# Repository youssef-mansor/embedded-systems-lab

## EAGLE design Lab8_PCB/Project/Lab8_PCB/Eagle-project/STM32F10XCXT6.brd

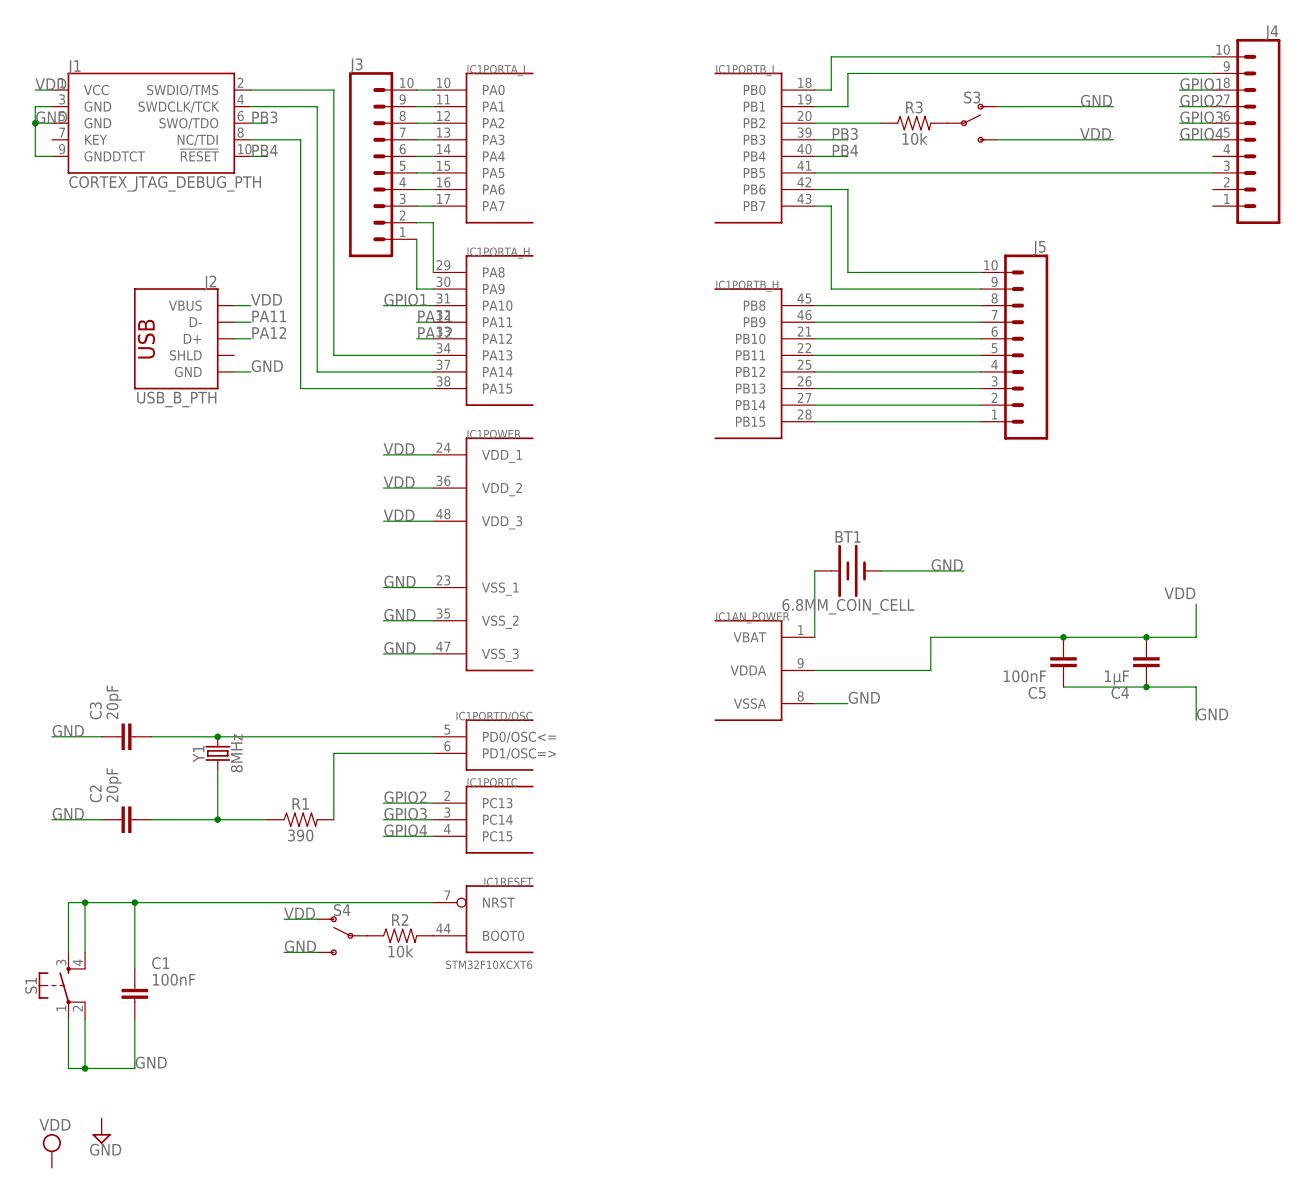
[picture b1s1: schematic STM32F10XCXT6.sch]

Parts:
BT1: 6.8MM_COIN_CELL; BATTCON-6.8MM
IC1: STM32F10XCXT6; TQFP48
J1: CORTEX_JTAG_DEBUG_PTH; 2X5-PTH-1.27MM
J2: USB_B_PTH; USB-B-PTH
J3, J4, J5: CONN_10"; 1X10
R1: 390; 0603
R2, R3: 10k; 0402
S1: MOMENTARY-SWITCH-SPST-2-SMD-4.6X2.8MM; TACTILE_SWITCH_SMD_4.6X2.8MM
S3, S4: SWITCH-SPDT-PTH-8.6X4.3MM; SWITCH_SPDT_8.6X4.3MM
Y1: 8MHz; CRYSTAL-PTH-2X6-CYL

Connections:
GND: BT1.-, IC1.8 (VSSA), IC1.23 (VSS_1), IC1.35 (VSS_2), IC1.47 (VSS_3), J1.3 (GND), J1.5 (GND), J1.9 (GNDDTCT), J2.GND, S1.1, S1.2, S3.1 (O), S4.3 (S)
GPIO1: IC1.31 (PA10), J4.8
GPIO2: IC1.2 (PC13), J4.7
GPIO3: IC1.3 (PC14), J4.6
GPIO4: IC1.4 (PC15), J4.5
unnamed: IC1.10 (PA0), J3.10
unnamed: IC1.7 (NRST), S1.3, S1.4
unnamed: IC1.5 (PD0/OSC<=), Y1.2
unnamed: IC1.6 (PD1/OSC=>), R1.2
unnamed: R1.1, Y1.1
unnamed: IC1.44 (BOOT0), R2.2
unnamed: R2.1, S4.2
unnamed: IC1.20 (PB2), R3.1
unnamed: R3.2, S3.2
unnamed: IC1.34 (PA13), J1.2 (SWDIO/TMS)
unnamed: IC1.37 (PA14), J1.4 (SWDCLK/TCK)
unnamed: IC1.38 (PA15), J1.8 (NC/TDI)
unnamed: BT1.+, IC1.1 (VBAT)
unnamed: IC1.45 (PB8), J5.8
unnamed: IC1.46 (PB9), J5.7
unnamed: IC1.21 (PB10), J5.6
unnamed: IC1.22 (PB11), J5.5
unnamed: IC1.25 (PB12), J5.4
unnamed: IC1.26 (PB13), J5.3
unnamed: IC1.27 (PB14), J5.2
unnamed: IC1.28 (PB15), J5.1
unnamed: IC1.18 (PB0), J4.10
unnamed: IC1.19 (PB1), J4.9
unnamed: IC1.41 (PB5), J4.3
unnamed: IC1.42 (PB6), J5.10
unnamed: IC1.43 (PB7), J5.9
unnamed: IC1.11 (PA1), J3.9
unnamed: IC1.12 (PA2), J3.8
unnamed: IC1.13 (PA3), J3.7
unnamed: IC1.14 (PA4), J3.6
unnamed: IC1.15 (PA5), J3.5
unnamed: IC1.16 (PA6), J3.4
unnamed: IC1.17 (PA7), J3.3
unnamed: IC1.29 (PA8), J3.2
unnamed: IC1.30 (PA9), J3.1
PA11: IC1.32 (PA11), J2.D-
PA12: IC1.33 (PA12), J2.D+
PB3: IC1.39 (PB3), J1.6 (SWO/TDO)
PB4: IC1.40 (PB4), J1.10 (!RESET)
VDD: IC1.9 (VDDA), IC1.24 (VDD_1), IC1.36 (VDD_2), IC1.48 (VDD_3), J1.1 (VCC), J2.VBUS, S3.3 (S), S4.1 (O)

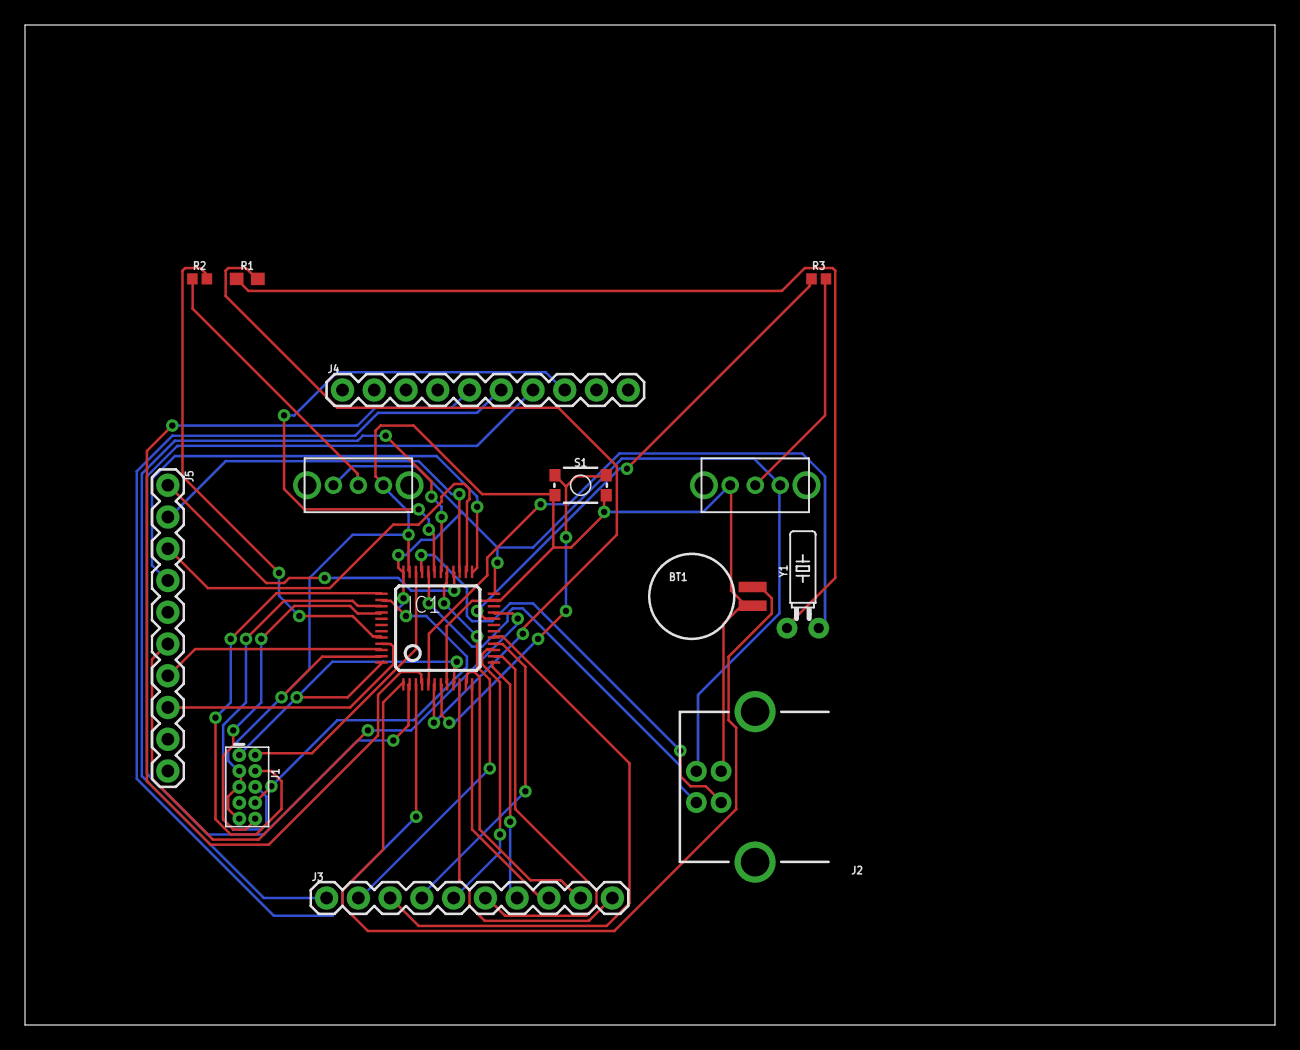
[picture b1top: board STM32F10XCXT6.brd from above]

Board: 2 copper layers, 100.0 x 80.0 mm, 14 parts (0 on the bottom side), 45 nets.

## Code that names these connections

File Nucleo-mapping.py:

#!/usr/bin/env python3
"""
STM32 Nucleo-L432KC: STM32 Pin to Arduino Label Mapper
"""

def get_pin_to_arduino():
    """Maps STM32 pin names to Arduino labels"""
    
    mapping = {
        # CN3 Left Side
        'PA9': 'D1',
        'PA10': 'D0',
        'PA12': 'D2',
        'PB0': 'D3',
        'PB7': 'D4',
        'PB6': 'D5',
        'PB1': 'D6',
        'PC14': 'D7',
        'PC15': 'D8',
        'PA8': 'D9',
        'PA11': 'D10',
        'PB5': 'D11',
        'PB4': 'D12',
        
        # CN4 Right Side
        'PA2': 'A7',
        'PA7': 'A6',
        'PA6': 'A5',
        'PA5': 'A4',
        'PA4': 'A3',
        'PA3': 'A2',
        'PA1': 'A1',
        'PA0': 'A0',
        'PB3': 'D13'
    }
    
    return mapping

def main():
    mapping = get_pin_to_arduino()
    
    print("=" * 40)
    print("Nucleo-L432KC Pin Mapper")
    print("=" * 40)
    print(f"{'STM32 Pin':^18} | {'Arduino Label':^18}")
    print("-" * 40)
    
    for stm_pin, arduino_label in sorted(mapping.items()):
        print(f"{stm_pin:^18} | {arduino_label:^18}")
    
    print("=" * 40)
    print("\nEnter STM32 pin (e.g., PA10, PB7) or 'quit'\n")
    
    while True:
        user_input = input("Enter pin: ").strip().upper()
        
        if user_input.lower() == 'quit':
            print("Goodbye!")
            break
        
        if not user_input:
            continue
        
        if user_input in mapping:
            print(f"  {user_input} → {mapping[user_input]}\n")
        else:
            print(f"  {user_input} not found\n")

if __name__ == "__main__":
    main()

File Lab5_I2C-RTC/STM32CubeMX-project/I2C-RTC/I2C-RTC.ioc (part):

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Mcu.Name=STM32L432K(B-C)Ux
Mcu.Package=UFQFPN32
Mcu.UserName=STM32L432KCUx
PA0.GPIOParameters=GPIO_Label
PA0.GPIO_Label=MCO [High speed clock in]
PA0.Mode=HSE-External-Clock-Source-for-LittleOrca
PA0.Signal=RCC_CK_IN
PA10.Mode=I2C
PA10.Signal=I2C1_SDA
PA13\ (JTMS-SWDIO).GPIOParameters=GPIO_Label
PA13\ (JTMS-SWDIO).GPIO_Label=SWDIO
PA13\ (JTMS-SWDIO).Mode=Serial_Wire
PA13\ (JTMS-SWDIO).Signal=SYS_JTMS-SWDIO
PA14\ (JTCK-SWCLK).GPIOParameters=GPIO_Label
PA14\ (JTCK-SWCLK).GPIO_Label=SWCLK
PA14\ (JTCK-SWCLK).Mode=Serial_Wire
PA14\ (JTCK-SWCLK).Signal=SYS_JTCK-SWCLK
PA15\ (JTDI).GPIOParameters=GPIO_Label
PA15\ (JTDI).GPIO_Label=VCP_RX
PA15\ (JTDI).Mode=Asynchronous
PA15\ (JTDI).Signal=USART2_RX
PA2.GPIOParameters=GPIO_Label
PA2.GPIO_Label=VCP_TX
PA2.Mode=Asynchronous
PA2.Signal=USART2_TX
PA5.Signal=GPIO_Output
PA7.Mode=I2C
PA7.Signal=I2C3_SCL
PA9.Mode=I2C
PA9.Signal=I2C1_SCL
PB4\ (NJTRST).Mode=I2C
PB4\ (NJTRST).Signal=I2C3_SDA
PC14-OSC32_IN\ (PC14).Mode=LSE-External-Oscillator
PC14-OSC32_IN\ (PC14).Signal=RCC_OSC32_IN
PC15-OSC32_OUT\ (PC15).Mode=LSE-External-Oscillator
PC15-OSC32_OUT\ (PC15).Signal=RCC_OSC32_OUT
RCC.HSE_VALUE=8000000
RCC.SYSCLKFreq_VALUE=14400000
RCC.SYSCLKSource=RCC_SYSCLKSOURCE_PLLCLK
board=NUCLEO-L432KC
boardIOC=true

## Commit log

2025-11-03 Add traffic light control with pause/resume using SW2 on TM4C123
2025-11-03 Add GPIOF / Systick interrupt control and implement interrupt-based traffic light system
2025-11-04 UART stuff
2025-11-04 SW increase decrease
2025-11-04 final before quiz
2025-11-11 Question: UART_Receive Enable calling in main
2025-11-16 Initialize DS3231 RTC, verify device readiness, set initial time, and stream live time over UART
2025-11-16 refactor into convenience functions
2025-11-16 Add DS3231 RTC Alarm 1 with buzzer functionality
2025-11-16 exp with poteniometer
2025-11-17 alarm2 experiment
2025-11-18 Implement real-time alarm configuration via UART for DS3231 RTC
2025-11-24 Implement deferred UART interrupt handling with FreeRTOS semaphore
2025-11-24 read temp and time from RTC
2025-12-02 Eagle project file, but copied from original path, some paths might break
2025-12-07 pwm buzzer song 1
2025-12-07 finish lab

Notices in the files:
parts and their libraries:
SparkFun-Batteries: Licensing: Creative Commons ShareAlike 4.0 International - https://creativecommons.org/licenses/by-sa/4.0
